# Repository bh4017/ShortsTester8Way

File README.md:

# ShortsTester8Way
A basic test jig for testing shorts on an 8-way connector.  This was made to help with production issues on an 8-way molex.

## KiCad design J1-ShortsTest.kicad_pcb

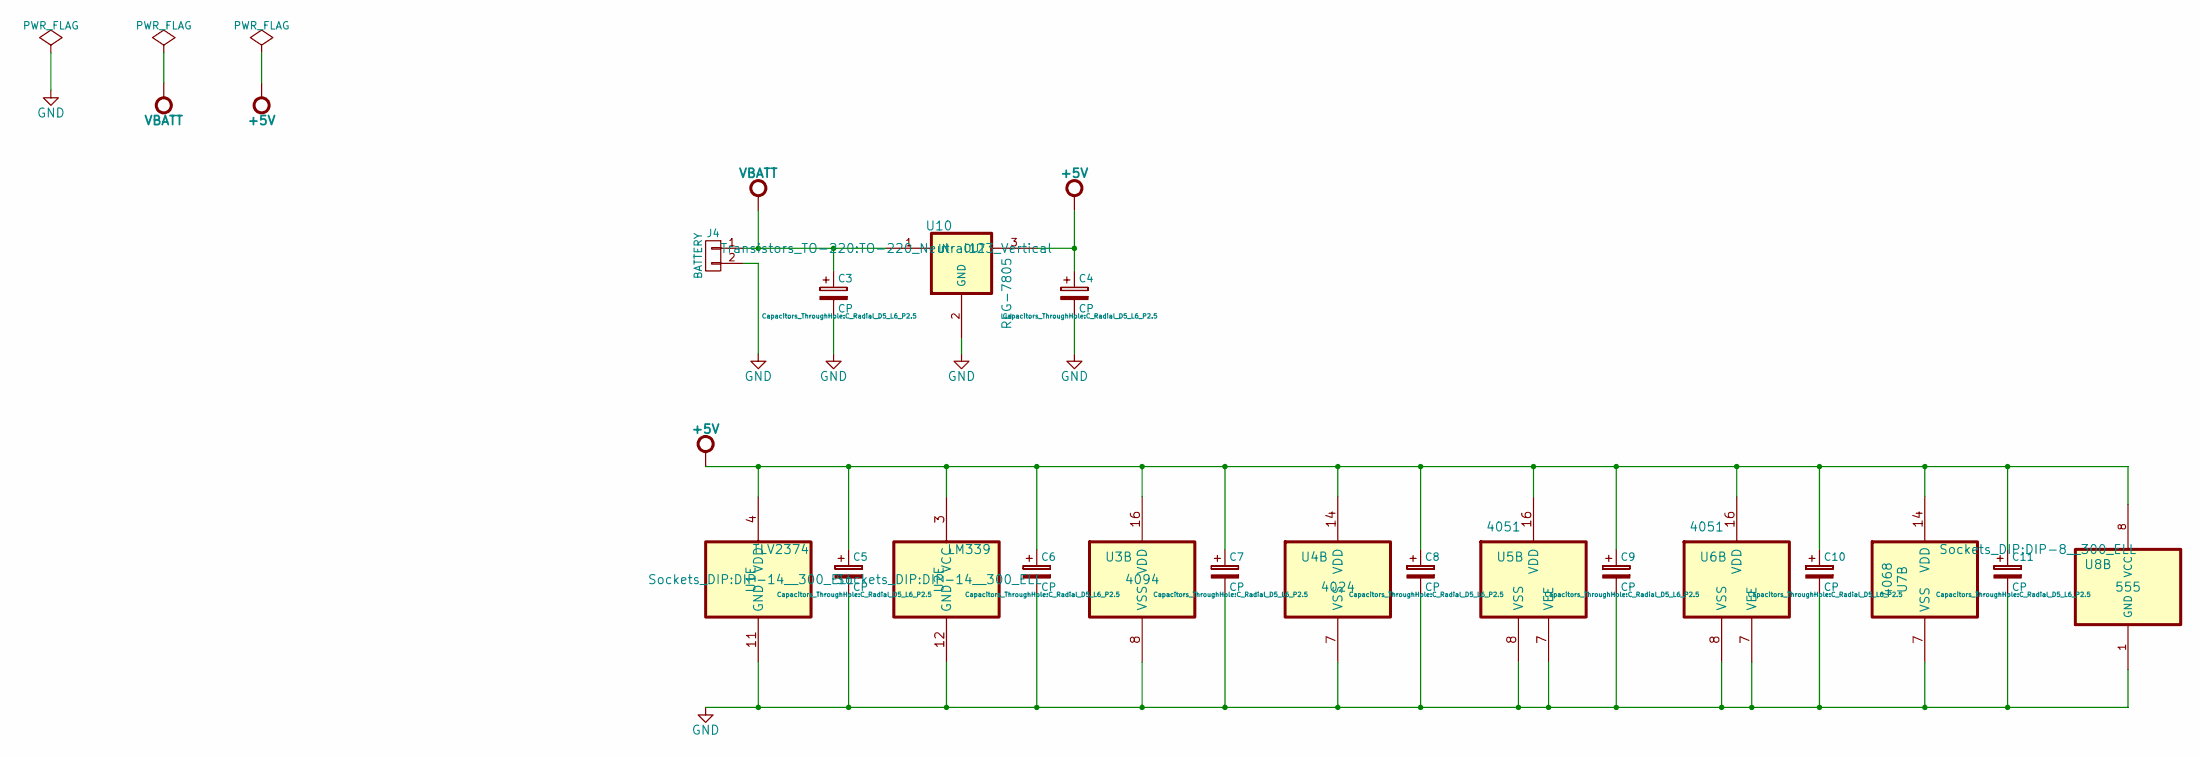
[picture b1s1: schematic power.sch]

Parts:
C3, C4, C5, C6, C7, C8, C9, C10, C11: CP; C_Radial_D5_L6_P2.5
J4: BATTERY; HEAD-1row-2.54mm-2way
U1: OpAmp-TLV2374; DIP-14__300_ELL
U2: Comp-LM339; DIP-14__300_ELL
U3: 4000series-4094; DIP-16__300_ELL
U4: 4000series-4024; DIP-14__300_ELL
U5, U6: 4000series-4051; DIP-16__300_ELL
U7: 4000series-4068; DIP-14__300_ELL
U8: 555_BJH; DIP-8__300_ELL
U10: REG-7805; TO-220_Neutral123_Vertical

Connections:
+5V: C4.1, C5.1, C6.1, C7.1, C8.1, C9.1, C10.1, C11.1, U1.4 (VDD), U2.3 (VCC), U3.16 (VDD), U4.14 (VDD), U5.16 (VDD), U6.16 (VDD), U7.14 (VDD), U8.8 (VCC), U10.3 (OUT); also elsewhere on the board
GND: C3.2, C4.2, C5.2, C6.2, C7.2, C8.2, C9.2, C10.2, C11.2, J4.2, U1.11 (GND), U2.12 (GND), U3.8 (VSS), U4.7 (VSS), U5.7 (VEE), U5.8 (VSS), U6.7 (VEE), U6.8 (VSS), U7.7 (VSS), U8.1 (GND), U10.2 (GND); also elsewhere on the board
VBATT: C3.1, J4.1, U10.1 (IN); also elsewhere on the board

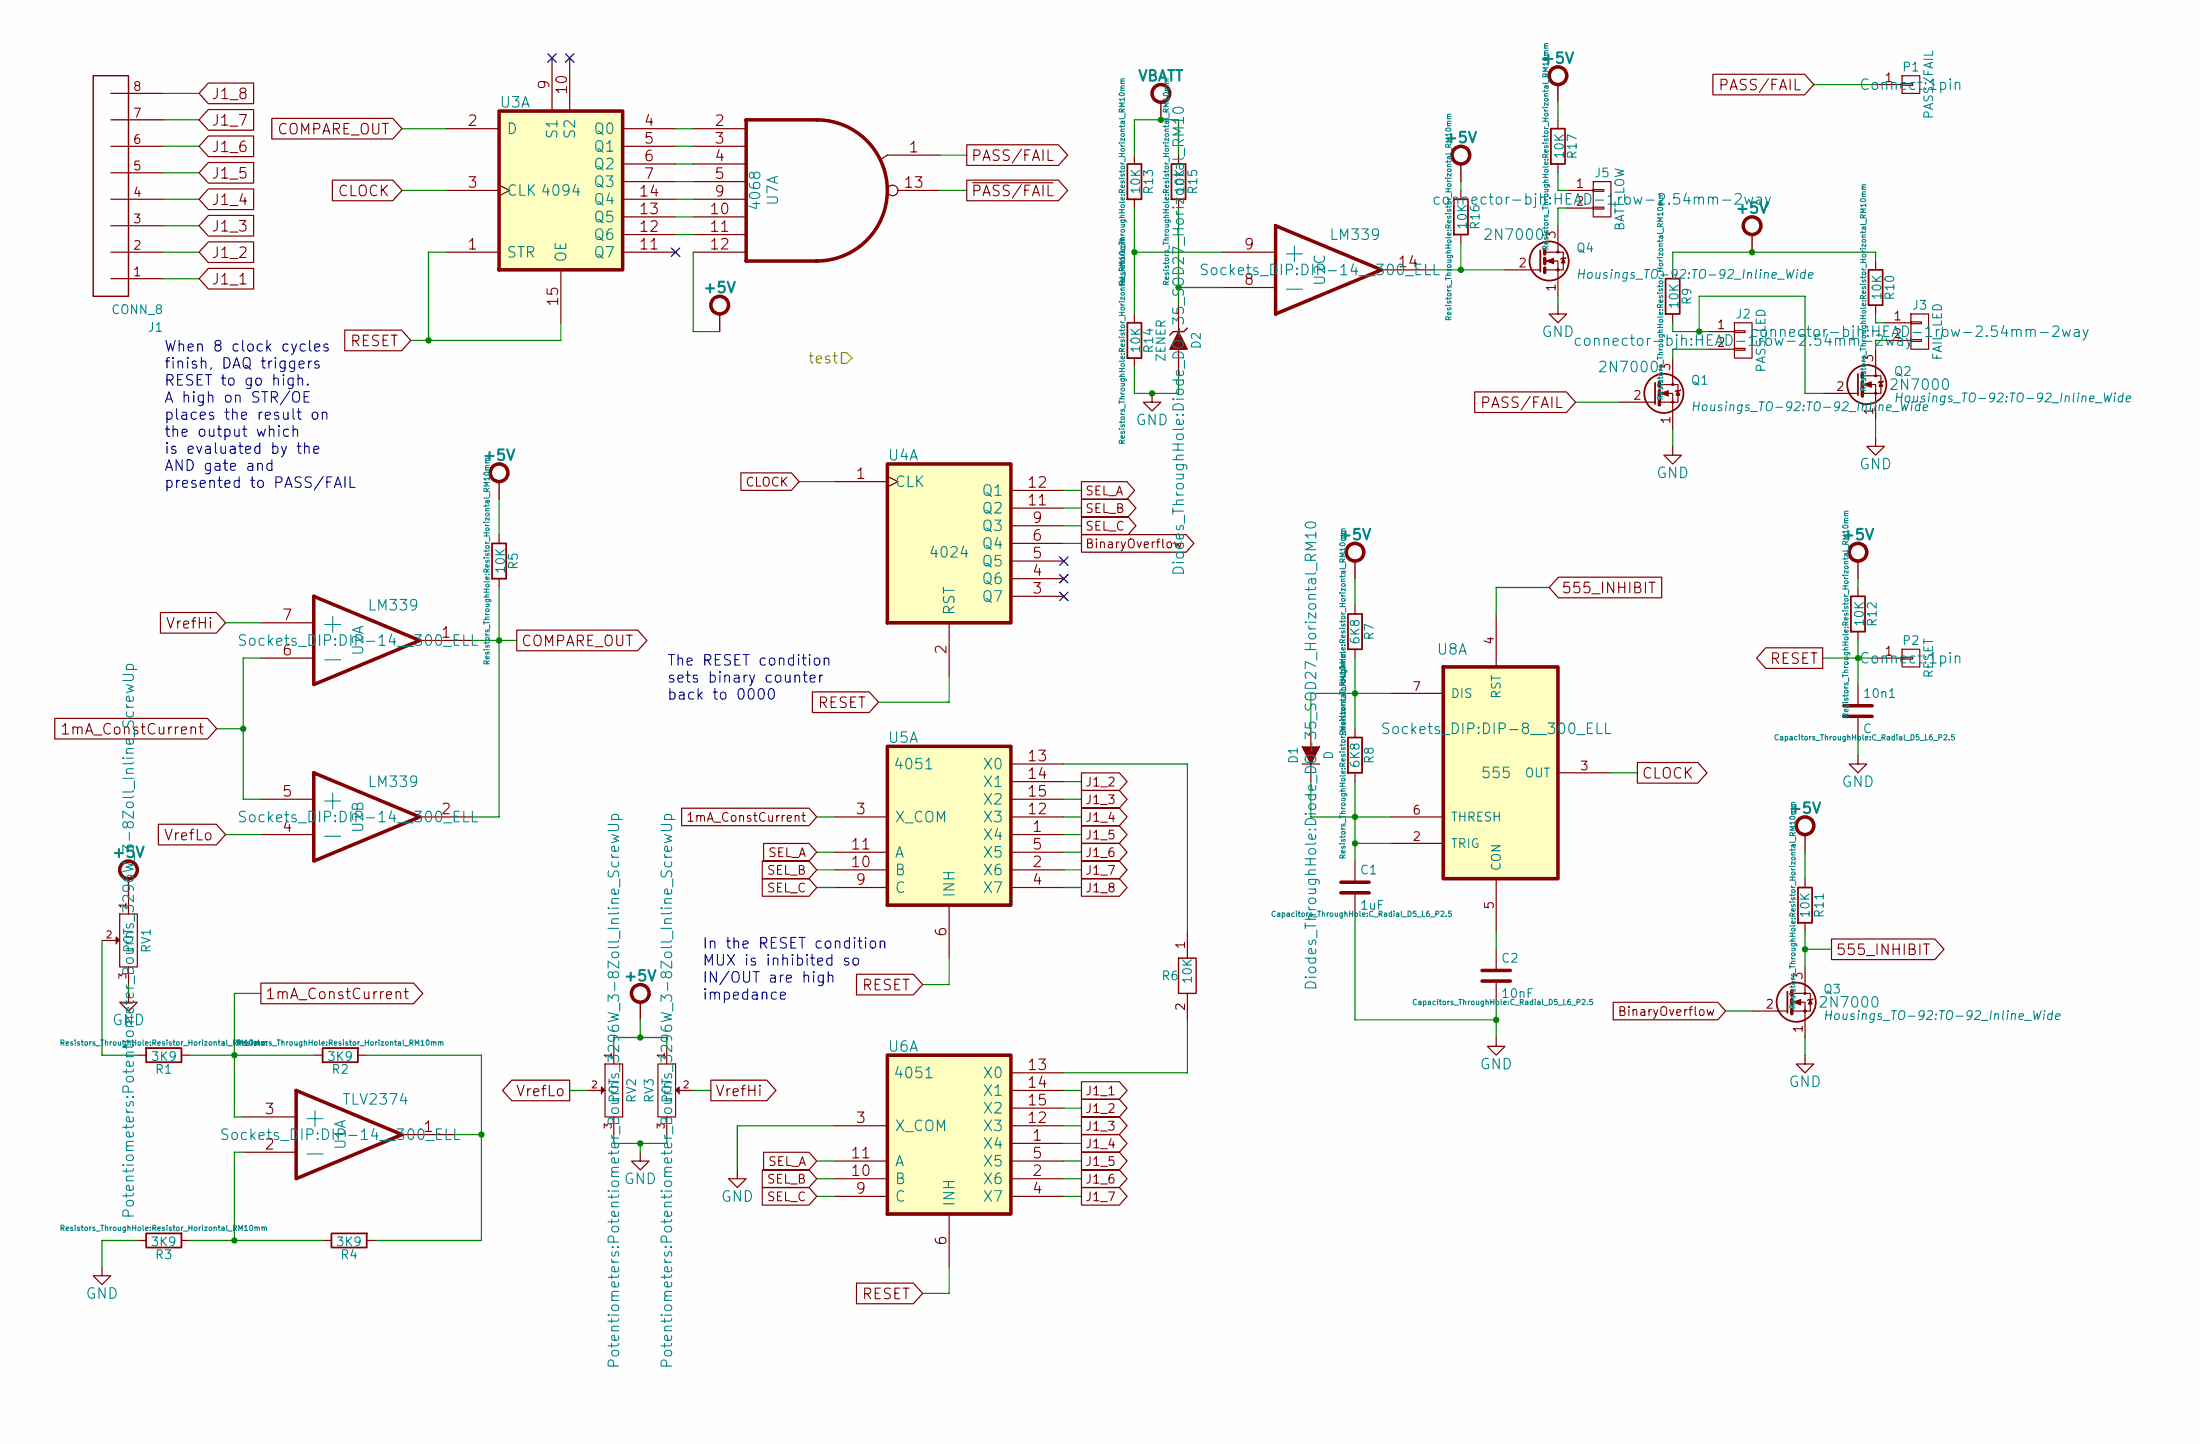
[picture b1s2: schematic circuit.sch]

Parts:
10n1: C; C_Radial_D5_L6_P2.5
C1: 1uF; C_Radial_D5_L6_P2.5
C2: 10nF; C_Radial_D5_L6_P2.5
D1: D; Diode_DO-35_SOD27_Horizontal_RM10
D2: ZENER; Diode_DO-35_SOD27_Horizontal_RM10
J1: CONN_8; HEAD-1row-2.54mm-8way
J2: PASS_LED; HEAD-1row-2.54mm-2way
J3: FAIL_LED; HEAD-1row-2.54mm-2way
J5: BATT_LOW; HEAD-1row-2.54mm-2way
P1: PASS/FAIL; 1pin
P2: RESET; 1pin
Q1, Q2, Q3, Q4: FET-2N7000; TO-92_Inline_Wide
R1, R2, R3, R4: 3K9; Resistor_Horizontal_RM10mm
R5, R6, R9, R10, R11, R12, R13, R14, R15, R16, R17: 10K; Resistor_Horizontal_RM10mm
R7, R8: 6K8; Resistor_Horizontal_RM10mm
RV1, RV2, RV3: POT; Potentiometer_Bourns_3296W_3-8Zoll_Inline_ScrewUp
U1: OpAmp-TLV2374; DIP-14__300_ELL
U2: Comp-LM339; DIP-14__300_ELL
U3: 4000series-4094; DIP-16__300_ELL
U4: 4000series-4024; DIP-14__300_ELL
U5, U6: 4000series-4051; DIP-16__300_ELL
U7: 4000series-4068; DIP-14__300_ELL
U8: 555_BJH; DIP-8__300_ELL

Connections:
1mA_ConstCurrent: R1.1, R2.1, U1.3 (+), U2.5 (+), U2.6 (-), U5.3 (X_COM)
555_INHIBIT: Q3.3 (D), R11.2, U8.4 (RST)
+5V: R5.1, R7.1, R9.1, R10.1, R11.1, R12.1, R16.1, R17.1, RV1.1, RV2.1, RV3.1, U7.12; also elsewhere on the board
BinaryOverflow: Q3.2 (G), U4.6 (Q4)
CLOCK: U3.3 (CLK), U4.1 (CLK), U8.3 (OUT)
COMPARE_OUT: R5.2, U2.1, U2.2, U3.2 (D)
GND: 10n1.2, C1.2, C2.2, D2.2 (A), Q1.1 (S), Q2.1 (S), Q3.1 (S), Q4.1 (S), R3.1, R14.2, RV1.3, RV2.3, RV3.3, U6.3 (X_COM); also elsewhere on the board
J1_1: J1.1, U6.14 (X1)
J1_2: J1.2, U5.14 (X1), U6.15 (X2)
J1_3: J1.3, U5.15 (X2), U6.12 (X3)
J1_4: J1.4, U5.12 (X3), U6.1 (X4)
J1_5: J1.5, U5.1 (X4), U6.5 (X5)
J1_6: J1.6, U5.5 (X5), U6.2 (X6)
J1_7: J1.7, U5.2 (X6), U6.4 (X7)
J1_8: J1.8, U5.4 (X7)
unnamed: C1.1, D1.1 (K), R8.2, U8.2 (TRIG), U8.6 (THRESH)
unnamed: C2.1, U8.5 (CON)
unnamed: D1.2 (A), R7.2, R8.1, U8.7 (DIS)
unnamed: D2.1 (K), R15.2, U2.8 (-)
unnamed: J2.1, Q2.2 (G), R9.2
unnamed: J2.2, Q1.3 (D)
unnamed: J3.1, R10.2
unnamed: J3.2, Q2.3 (D)
unnamed: J5.1, R17.2
unnamed: J5.2, Q4.3 (D)
unnamed: Q4.2 (G), R16.2, U2.14
unnamed: R1.2, RV1.2
unnamed: R2.2, R4.2, U1.1
unnamed: R3.2, R4.1, U1.2 (-)
unnamed: R6.1, U5.13 (X0)
unnamed: R6.2, U6.13 (X0)
unnamed: R13.2, R14.1, U2.9 (+)
unnamed: U3.4 (Q0), U7.2
unnamed: U3.5 (Q1), U7.3
unnamed: U3.6 (Q2), U7.4
unnamed: U3.7 (Q3), U7.5
unnamed: U3.12 (Q6), U7.11
unnamed: U3.13 (Q5), U7.10
unnamed: U3.14 (Q4), U7.9
PASS/FAIL: P1.1, Q1.2 (G), U7.1
RESET: 10n1.1, P2.1, R12.2, U3.1 (STR), U3.15 (OE), U4.2 (RST), U5.6 (INH), U6.6 (INH)
SEL_A: U4.12 (Q1), U5.11 (A), U6.11 (A)
SEL_B: U4.11 (Q2), U5.10 (B), U6.10 (B)
SEL_C: U4.9 (Q3), U5.9 (C), U6.9 (C)
VBATT: R13.1, R15.1; also elsewhere on the board
VrefHi: RV3.2, U2.7 (+)
VrefLo: RV2.2, U2.4 (-)
~PASS/FAIL: U7.13

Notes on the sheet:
When 8 clock cycles finish, DAQ triggers RESET to go high. A high on STR/OE places the result on the output which is evaluated by the AND gate and presented to PASS/FAIL
In the RESET condition MUX is inhibited so IN/OUT are high impedance
The RESET condition sets binary counter back to 0000

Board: 2 copper layers, 54 parts (0 on the bottom side), 47 nets, no tracks yet.

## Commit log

2015-09-29 more work on the schematic
2015-10-02 Added battery low detector and stripboard design (VeeCad)
2015-10-02 Separated .net files for VeeCAD and KiCAD. Associated footprints for KiCAD and started board layout
2015-10-04 Completed PCB layout
